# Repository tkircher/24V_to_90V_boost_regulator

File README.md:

# 24V_to_90V_boost_regulator
This is a boost regulator to generate 90V to power my coffee grinder DC motor from 24V DC

This PCB is from a first revision. I used it to successfully power my 90V DC treadmill motor under moderate load.

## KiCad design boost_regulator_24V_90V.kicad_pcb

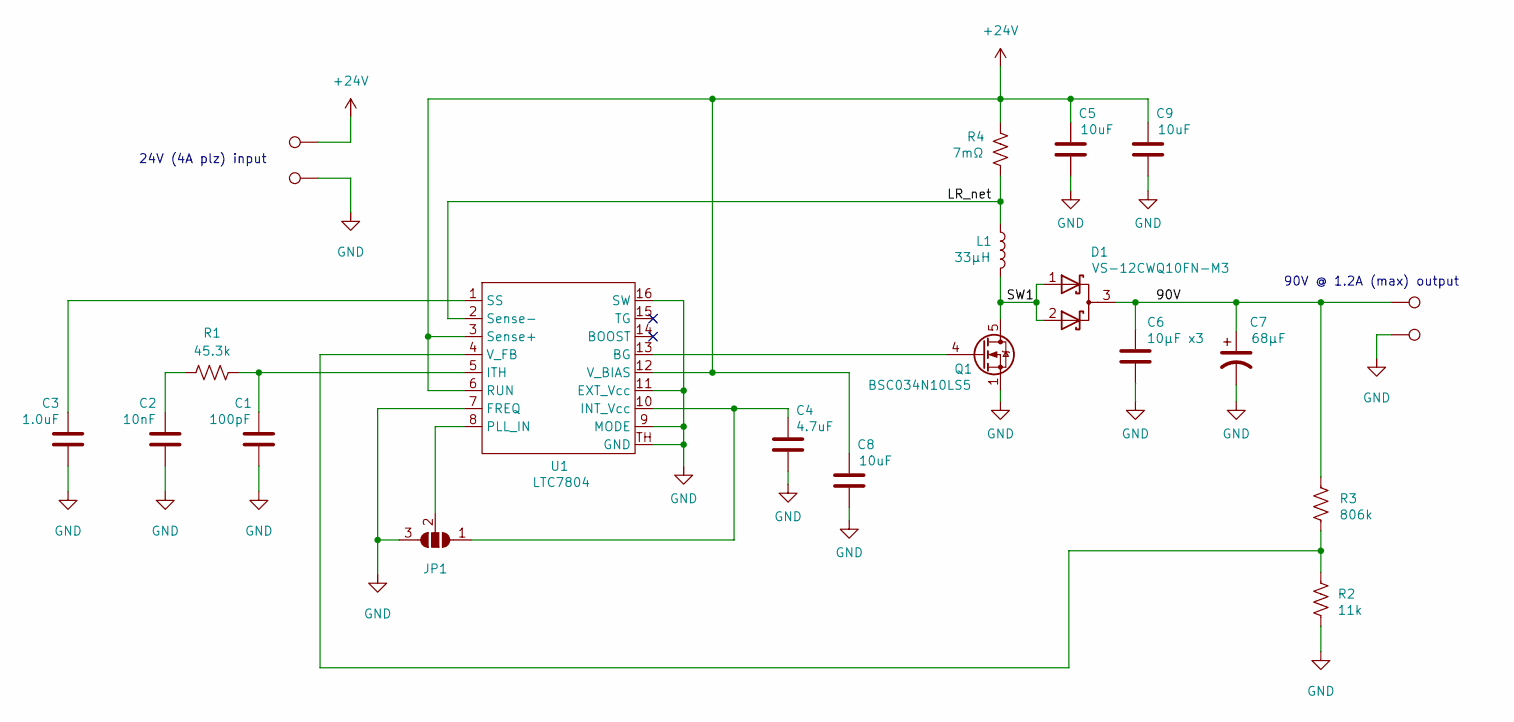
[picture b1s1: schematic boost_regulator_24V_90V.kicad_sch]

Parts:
C1: 100pF; C_0805_2012Metric
C2: 10nF; C_0805_2012Metric
C3: 1.0uF; C_0805_2012Metric
C4: 4.7uF; R_0805_2012Metric
C5, C8, C9: 10uF; R_1210_3225Metric
C6: 10µF x3; C_2220_5650Metric
C7: 68µF; AFK_H
Conn1: 90V; TestPoint_THTPad_4.0x4.0mm_Drill2.0mm
Conn2: 24V; TestPoint_THTPad_4.0x4.0mm_Drill2.0mm
Conn3, Conn4: GND; TestPoint_THTPad_4.0x4.0mm_Drill2.0mm
D1: VS-12CWQ10FN-M3; D-PAK
JP1: Spread spectrum select; SolderJumper-3_P1.3mm_Open_Pad1.0x1.5mm
L1: 33µH; SRP1510CA
Q1: BSC034N10LS5; TDSON-8-1
R1: 45.3k; R_0805_2012Metric
R2: 11k; R_0805_2012Metric
R3: 806k; R_0805_2012Metric
R4: 7mΩ; WSHM2818
U1: LTC7804; LTC7804_MSOP

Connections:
+24V: C5.1, C8.1, C9.1, Conn2.1, R4.2, U1.3 (Sense+), U1.6 (RUN), U1.12 (V_BIAS)
/90V: C6.1, C7.1, Conn1.1, D1.3 (A), R3.1
/LR_net: L1.1, R4.1, U1.2 (Sense-)
/SW1: D1.1 (K), D1.2 (K), L1.2, Q1.5 (D)
GND: C1.2, C2.2, C3.2, C4.2, C5.2, C6.2, C7.2, C8.2, C9.2, Conn3.1, Conn4.1, JP1.3 (B), Q1.1 (S), Q1.2 (S), Q1.3 (S), R2.2, U1.7 (FREQ), U1.9 (MODE), U1.11 (EXT_Vcc), U1.16 (SW), U1.TH (GND)
unnamed: C2.1, R1.2
unnamed: C4.1, JP1.1 (A), U1.10 (INT_Vcc)
unnamed: JP1.2 (C), U1.8 (PLL_IN)
unnamed: Q1.4 (G), U1.13 (BG)
unnamed: C1.1, R1.1, U1.5 (ITH)
unnamed: C3.1, U1.1 (SS)
unnamed: R2.1, R3.2, U1.4 (V_FB)

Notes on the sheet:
90V @ 1.2A (max) output
24V (4A plz) input

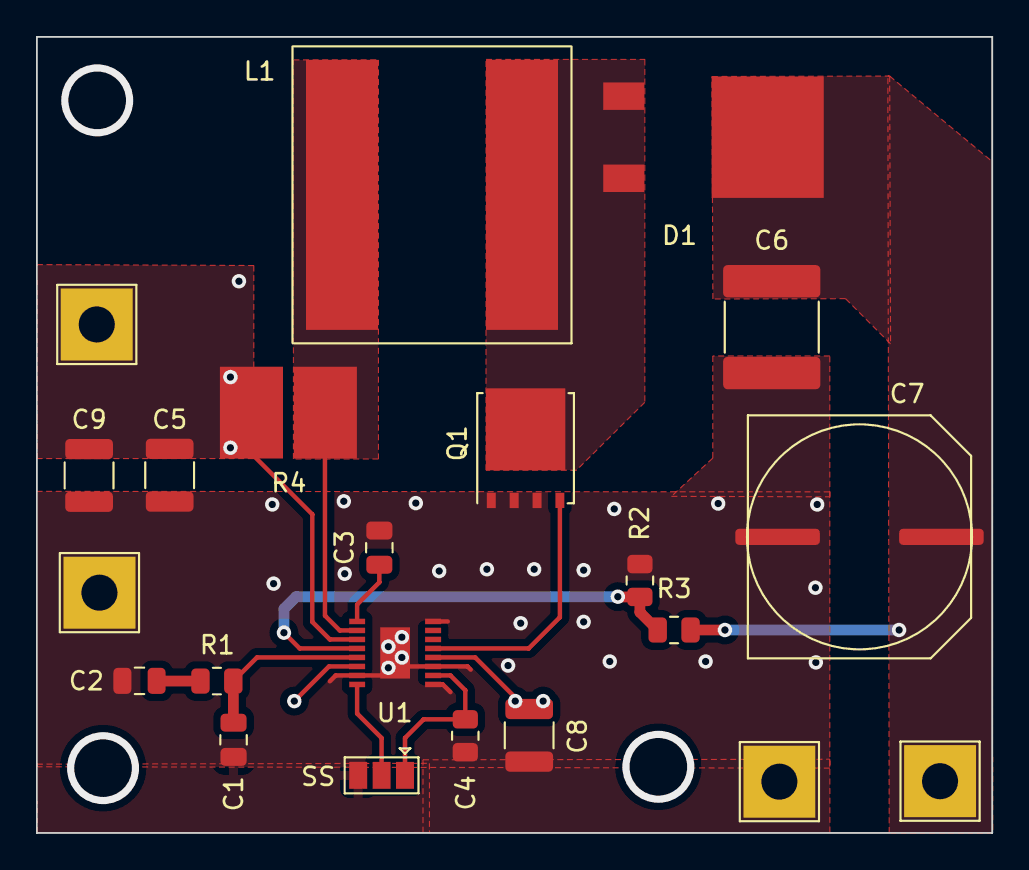
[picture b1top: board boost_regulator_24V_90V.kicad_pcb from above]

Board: 2 copper layers, 53.1 x 44.2 mm, 22 parts (0 on the bottom side), 12 nets.
